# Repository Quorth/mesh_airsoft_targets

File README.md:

# mesh_airsoft_targets

Completed targets (piezo still not glued)

An arduino based airsoft targets with mesh networking capabilities. This is a WIP project originally made for the Murcia Lan Party event. But since it's been stalled for more than a year, we decided to release

We use the nrlf24l01 2.4Ghz modem and the RF24Mesh library to comunicate the targets with the master module

First boards

The targets can control a RGB LED and reports the impacts to the master node, the games are implemented in the master module, so far we only have a sequential game with timing implemented

The impact detection is implemented via a piezoelectric transducer and a opamp for cleaning the pulse and setting sensitivity, you have the eagle schematics in target_node/board

Detecting an impact

The master module is an arduino board with a serial connection to the host the same board we use for the targets can be used as a master, but the idea is to eventually port to an OpenWRT target (like a TL703n) for networked operation or a BT link to a phone.

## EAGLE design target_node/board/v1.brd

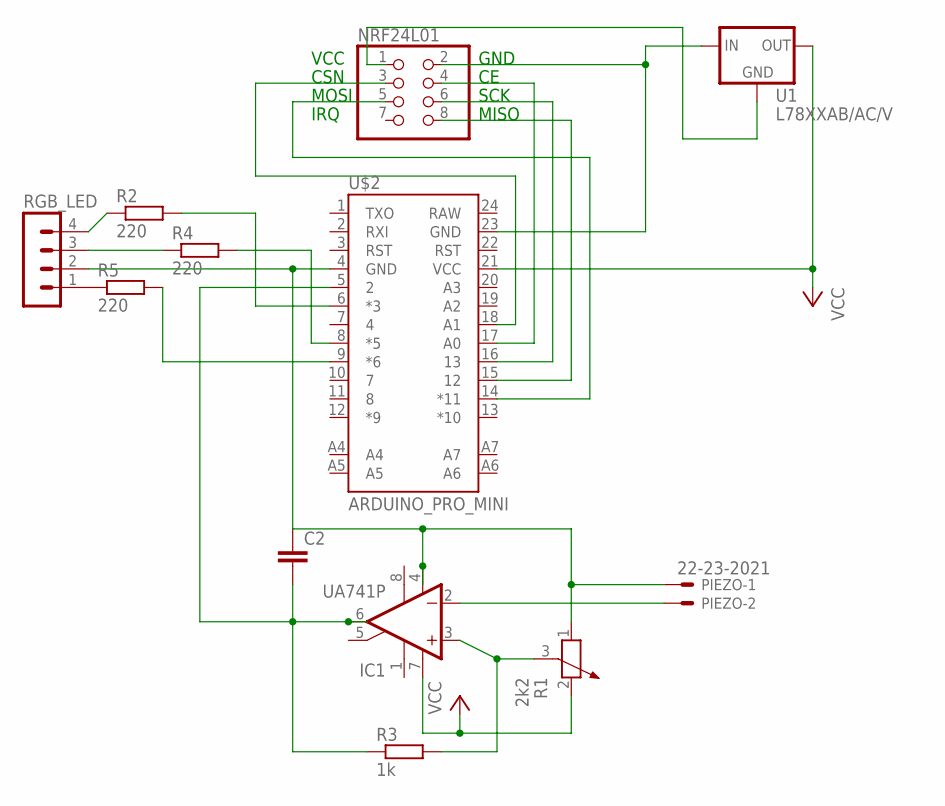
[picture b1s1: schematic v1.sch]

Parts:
C2: C-EU050-024X044; C050-024X044
IC1: UA741P; DIL08
NRF24L01: PINHD-2X4; 2X04
PIEZO: 22-23-2021
R1: 2k2; PT-10
R2, R4, R5: 220; 0207/10
R3: 1k; 0207/10
RGB_LED: MA04-1
U1: L78XXAB/AC/V; 78XXS
U$2: ARDUINO_PRO_MINI

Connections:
unnamed: NRF24L01.6, U$2.16 (13)
unnamed: NRF24L01.8, U$2.15 (12)
unnamed: NRF24L01.5, U$2.14 (*11)
unnamed: NRF24L01.4, U$2.17 (A0)
unnamed: R2.1, RGB_LED.4
unnamed: R4.1, RGB_LED.3
unnamed: R5.1, RGB_LED.1
unnamed: IC1.2 (-IN), PIEZO.2
unnamed: R2.2, U$2.6 (*3)
unnamed: R4.2, U$2.8 (*5)
unnamed: R5.2, U$2.9 (*6)
unnamed: C2.2, IC1.6 (OUT), R3.1, U$2.5 (2)
unnamed: NRF24L01.1, U1.GND
unnamed: NRF24L01.3, U$2.18 (A1)
unnamed: IC1.3 (+IN), R1.3, R3.2
unnamed: NRF24L01.2, U1.IN, U$2.23 (GND)
unnamed: C2.1, IC1.4 (V-), PIEZO.1, R1.1, RGB_LED.2, U$2.4 (GND)
VCC: IC1.7 (V+), R1.2, U1.OUT, U$2.21 (VCC)

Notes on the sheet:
VCC
GND
CSN
MOSI
SCK
IRQ
MISO

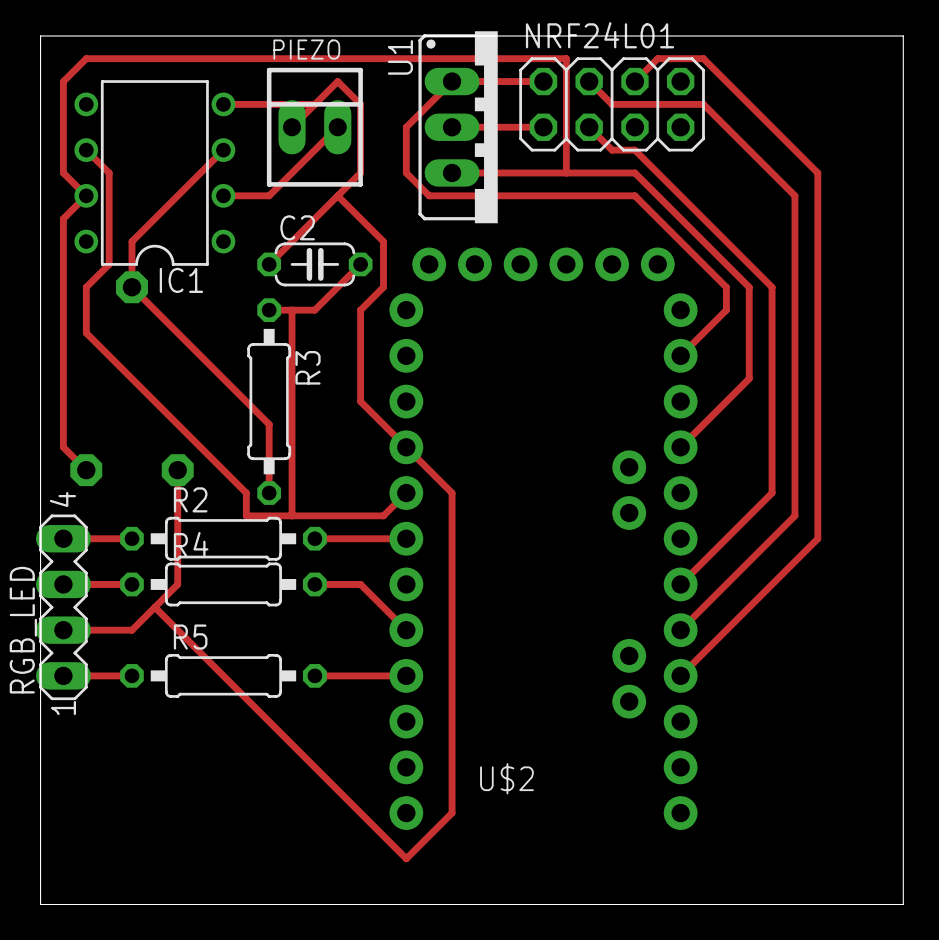
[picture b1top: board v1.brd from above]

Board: 2 copper layers, 47.9 x 48.2 mm, 12 parts (1 on the bottom side), 18 nets.

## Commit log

2015-11-11 Initial commit. Added basic flow based on RF24Mesh examples. Added also custom library and function files
2015-11-11 Moved declarations to lib_target.h Deleted led_pinout struct and replaced with a const int array
2015-11-11 Added led command rx case on node targets
2015-11-11 Implemented set_led_command function and starting coding update_leds function
2015-11-11 Added update_led implementation and 3 animations (off, on, blink and fast blink)
2015-11-11 added first test on light signals deleted custom libraries and functions on target_master folder - they were symbolic links of the same files on target_node folder and weren't working
2015-11-11 Fixed detection of multiple interrupts with a single shoot
2015-11-17 Reestructurados los directorios
2015-11-17 Added previous files & staging schematics
2015-11-17 Added first revision of the circuit and staging board
2015-11-19 Changed schematic to connect nRF24 board to other digital outputs and make a single layer board
2015-11-24 NODE BOARD: Changed schematic to easily fit on a single layered PCB -> CE and CS from nRF24 to pins 14 & 15 NODE FIRM: Changed CE and CS pins, changed interrupts from RISING to FALLING, changed folde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
2015-11-24 NODE FIRM: Added address renew command support
2015-11-24 MASTER FIRM: added node address renewing command
2015-11-24 NODE FIRM: Fixed renew address command, fixed led command copy (now it works! :D)
2015-11-24 MASTER FIRM: fixed node address renewing control
2015-11-25 MASTER FIRM: Implemented first game (beta) - compiled successfully
2015-11-26 NODE FIRM: several fixes on command RX
2015-11-26 MASTER FIRM: Tested and fixed sequential game (now it works! :D)
2017-01-09 add images

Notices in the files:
parts and their libraries:
SparkFun-Boards: Licensing: Creative Commons ShareAlike 4.0 International - https://creativecommons.org/licenses/by-sa/4.0
